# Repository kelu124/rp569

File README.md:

# rp569

An open hardware board (KiCad) that pairs a **Raspberry Pi RP2350B** with a **WCH CH569W**.
The RP2350B generates high-speed data and the CH569 streams it to a host over **USB 3.0**.

Status: **v1.0** (tag `v1.0`). Schematic complete, PCB **fully routed** (4-layer, 50×70 mm, rounded corners,
parts on both sides; 0 unconnected, 0 DRC errors) and **JLCPCB production files generated**. Before ordering:
USB pairs as coupled pairs, silkscreen cleanup, impedance check (see [`docs/layout.md`](docs/layout.md)).
First firmware for both chips in [`firmware/`](firmware/) (builds, not run on hardware yet).
[Schematic PDF](hardware/rp569-schematic.pdf). Documentation site: https://kelu124.github.io/rp569/ (GitHub Pages from `docs/`).

## Production files (JLCPCB)

| File | Use |
|---|---|
| [`hardware/jlcpcb/rp569-gerbers.zip`](hardware/jlcpcb/rp569-gerbers.zip) | PCB order (gerbers + drill) |
| [`hardware/jlcpcb/rp569-bom.csv`](hardware/jlcpcb/rp569-bom.csv) | Assembly BOM with LCSC part numbers |
| [`hardware/jlcpcb/rp569-cpl.csv`](hardware/jlcpcb/rp569-cpl.csv) | Assembly placement (CPL) |

Board to fabricate: [`hardware/rp569-routed.kicad_pcb`](hardware/rp569-routed.kicad_pcb). Regenerate the files
with `python3 hardware/gen/gen_fab.py`. Two parts are not stocked by JLCPCB and must be consigned: CH569W and the
Amphenol GSB343K33HR USB3 connector ([`docs/bom.md`](docs/bom.md)).

| Top | Bottom |
|---|---|
|  |  |

## Features

| Block | RP2350B | CH569W |
|-------|---------|--------|
| USB | USB 2.0 on USB-C (firmware, debug, test control) | USB 3.0 SuperSpeed, Micro-B connector |
| Storage | QSPI flash | SD card on the eMMC/SD controller |
| User I/O | RGB LED, 2 user buttons | RGB LED, 2 user buttons |
| Boot | BOOTSEL + RUN buttons | BOOT button + jumper (force the USB bootloader on a blank chip) |
| Breakout | I2C header for extra devices | I2C header (bit-banged GPIO) |

**Logic analyser**: 8 input pins on the RP2350B are sampled by PIO and streamed over the
parallel bus to the CH569, then to the host over USB 3.

**Power**: the RP2350B runs from either USB connector through a TI TPS2121 power mux, so neither back-feeds the
other. The CH569 is powered from its own USB3 VBUS through a load switch that the RP2350B controls, so
it can be power-cycled and forced into its bootloader during automated tests.

**Links between the two chips**
- 8-bit parallel bus with clock and handshake lines (8-bit because the CH569's 16-bit mode shares pins with the SD card; see [`specification.md`](specification.md) D-003): RP2350B PIO sends, CH569 HSPI receives.
- Shared I2C bus.
- UART.
- CH569 RESET# and boot-mode pins driven by the RP2350B, so the CH569 can be reflashed and
  power-cycled automatically during testing.

## Repository layout

| Path | Content |
|------|---------|
| `hardware/` | KiCad project, generated from `hardware/gen/board.py` (run `hardware/gen/build.sh`); `rp569-routed.kicad_pcb` = routed v1.0 board |
| `hardware/jlcpcb/` | JLCPCB production files: gerbers zip, BOM, CPL |
| `python/` | Host library: finds the RP2350/CH569 ports by VID/PID/product/UID, one method per firmware command (`python/README.md`) |
| `firmware/` | `rp2350/` USB command line (LED, `dfu`, CH569 power/boot/link), `ch569/` USB3 serial + SD drive with RP2350 link echo; see `firmware/README.md` |
| `datasheet/` | Datasheets as PDF and Markdown (see `datasheet/README.md`) |
| `docs/` | GitHub Pages site root (`index.md`, `_config.yml`): `architecture.md`, `production.md`, `pinmap.md` (RP2350B ↔ CH569 pin map), `power.md`, `layout.md`, `bom.md` (JLCPCB BOM), `ch569-hardware-notes.md`, `hadposts/` (Hackaday log drafts) |
| `project/` | Reference projects: [HydraUSB3](https://github.com/hydrausb3), [phantomdrive](https://github.com/o7-machinehum/phantomdrive) (see `project/README.md`) |
| `specification.md` | Requirements (R-xx) and design decisions (D-xxx) |
| `CLAUDE.md`, `.claude/` | Project context, todo/done logs, commit log |

## References

- [HydraUSB3](https://github.com/hydrausb3): open-source CH569 dev kit, firmware and HSPI/USB3 drivers.
- [phantomdrive](https://github.com/o7-machinehum/phantomdrive): open-source CH569W encrypted USB3 drive with SD card, KiCad sources.
- [RP2350 datasheet](https://datasheets.raspberrypi.com/rp2350/rp2350-datasheet.pdf) and
  [hardware design guide](https://datasheets.raspberrypi.com/rp2350/hardware-design-with-rp2350.pdf).

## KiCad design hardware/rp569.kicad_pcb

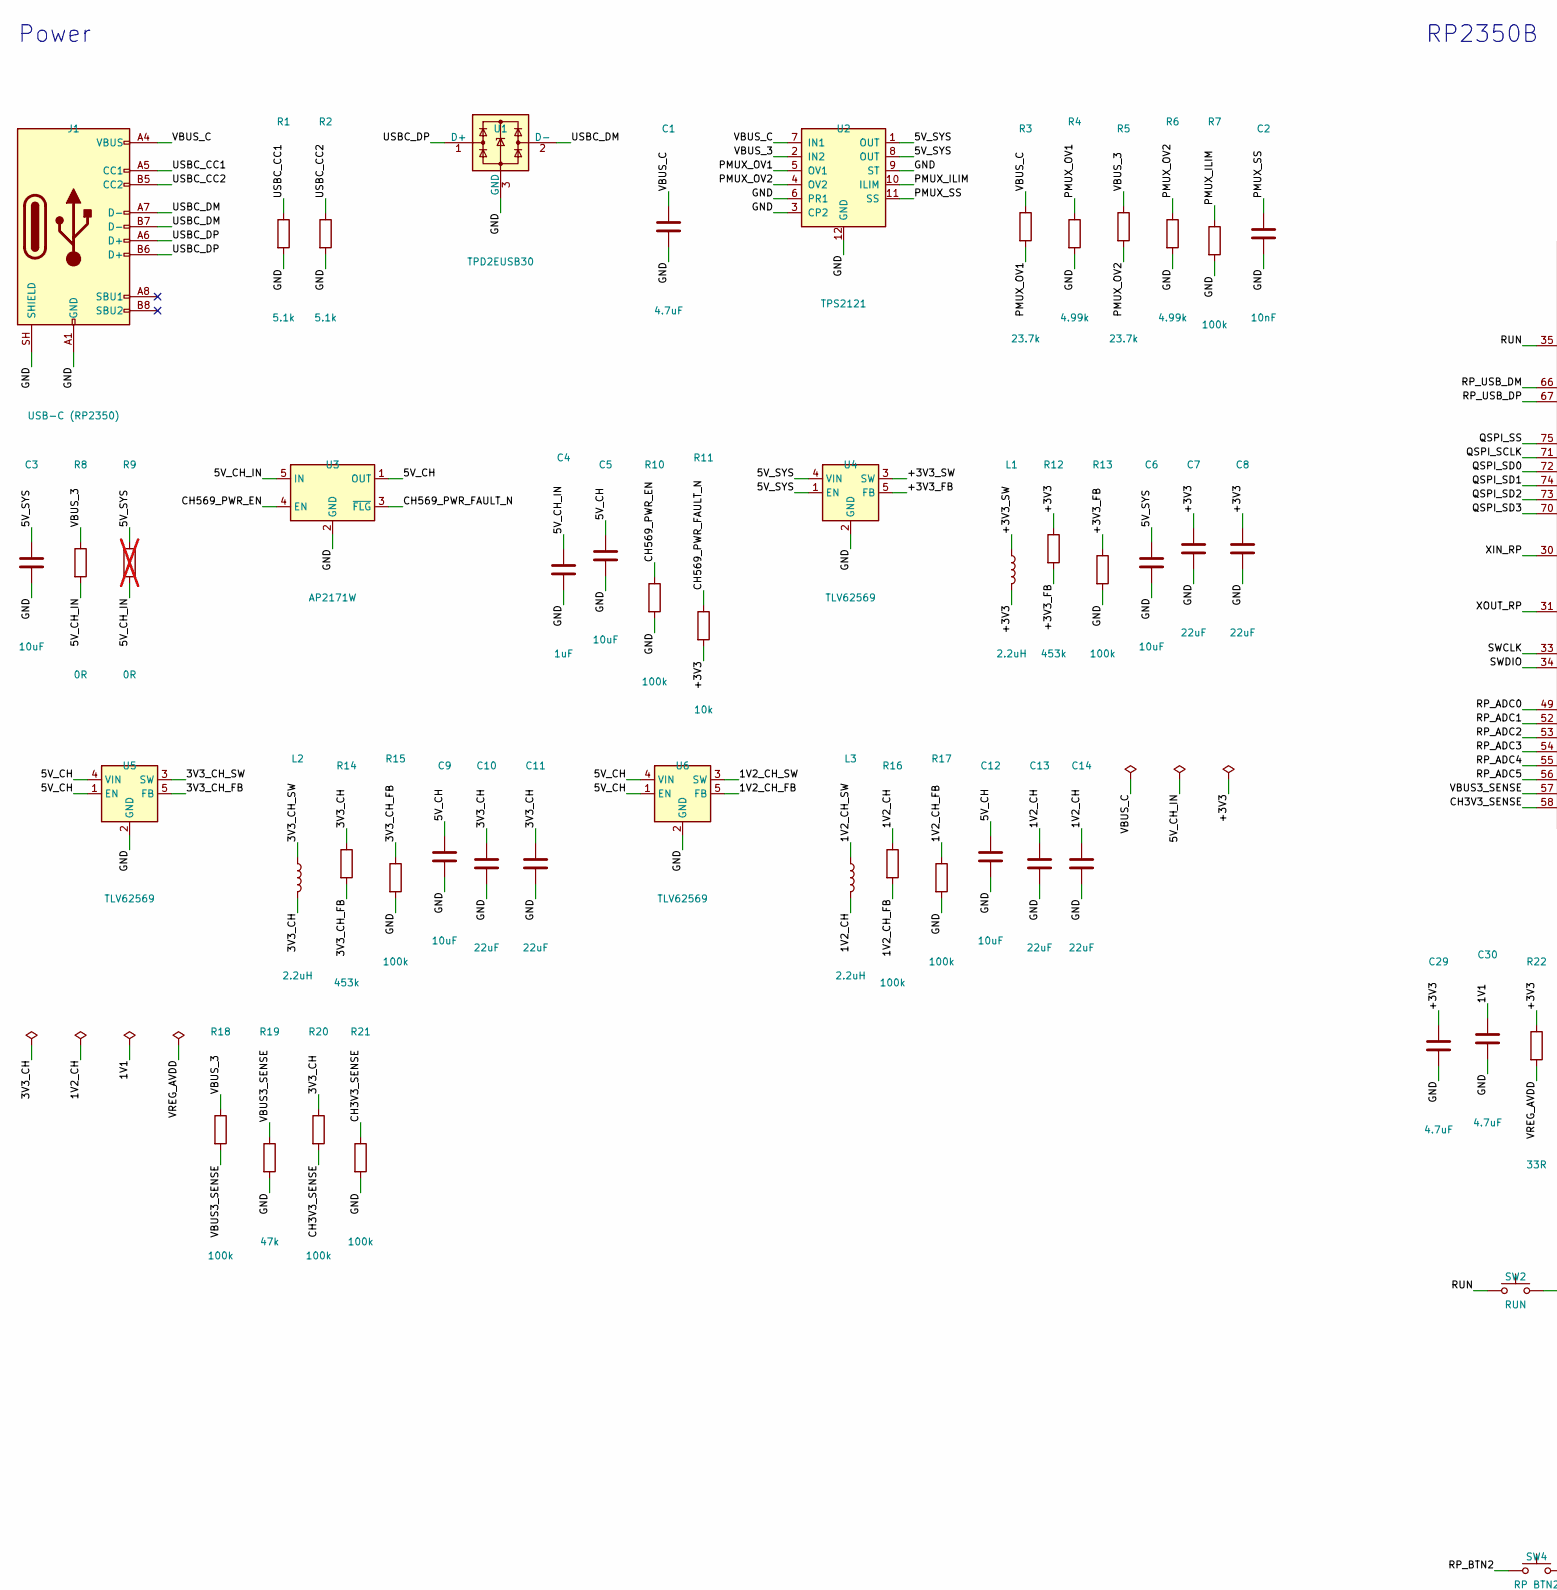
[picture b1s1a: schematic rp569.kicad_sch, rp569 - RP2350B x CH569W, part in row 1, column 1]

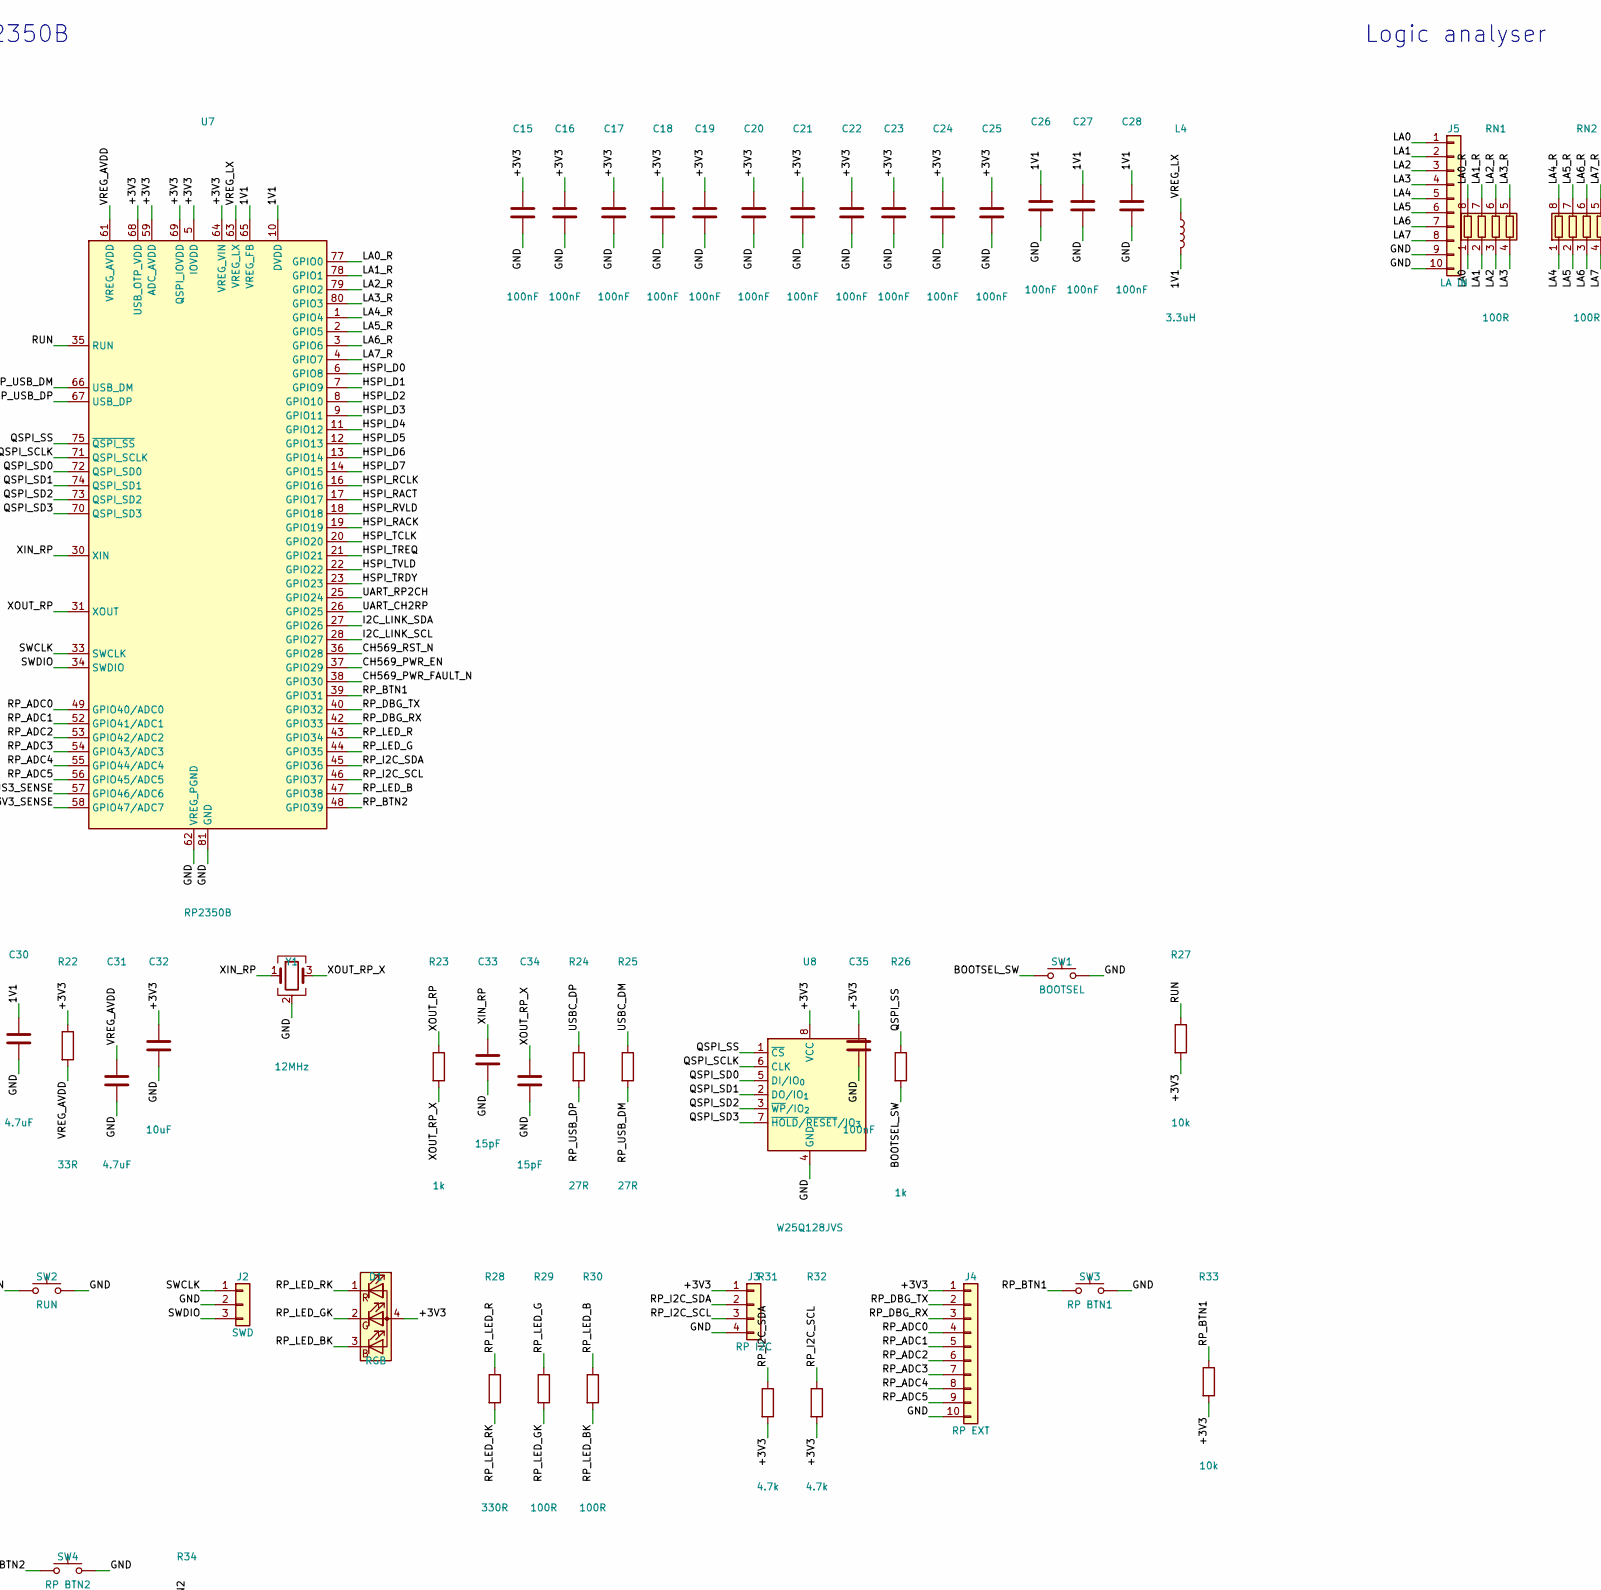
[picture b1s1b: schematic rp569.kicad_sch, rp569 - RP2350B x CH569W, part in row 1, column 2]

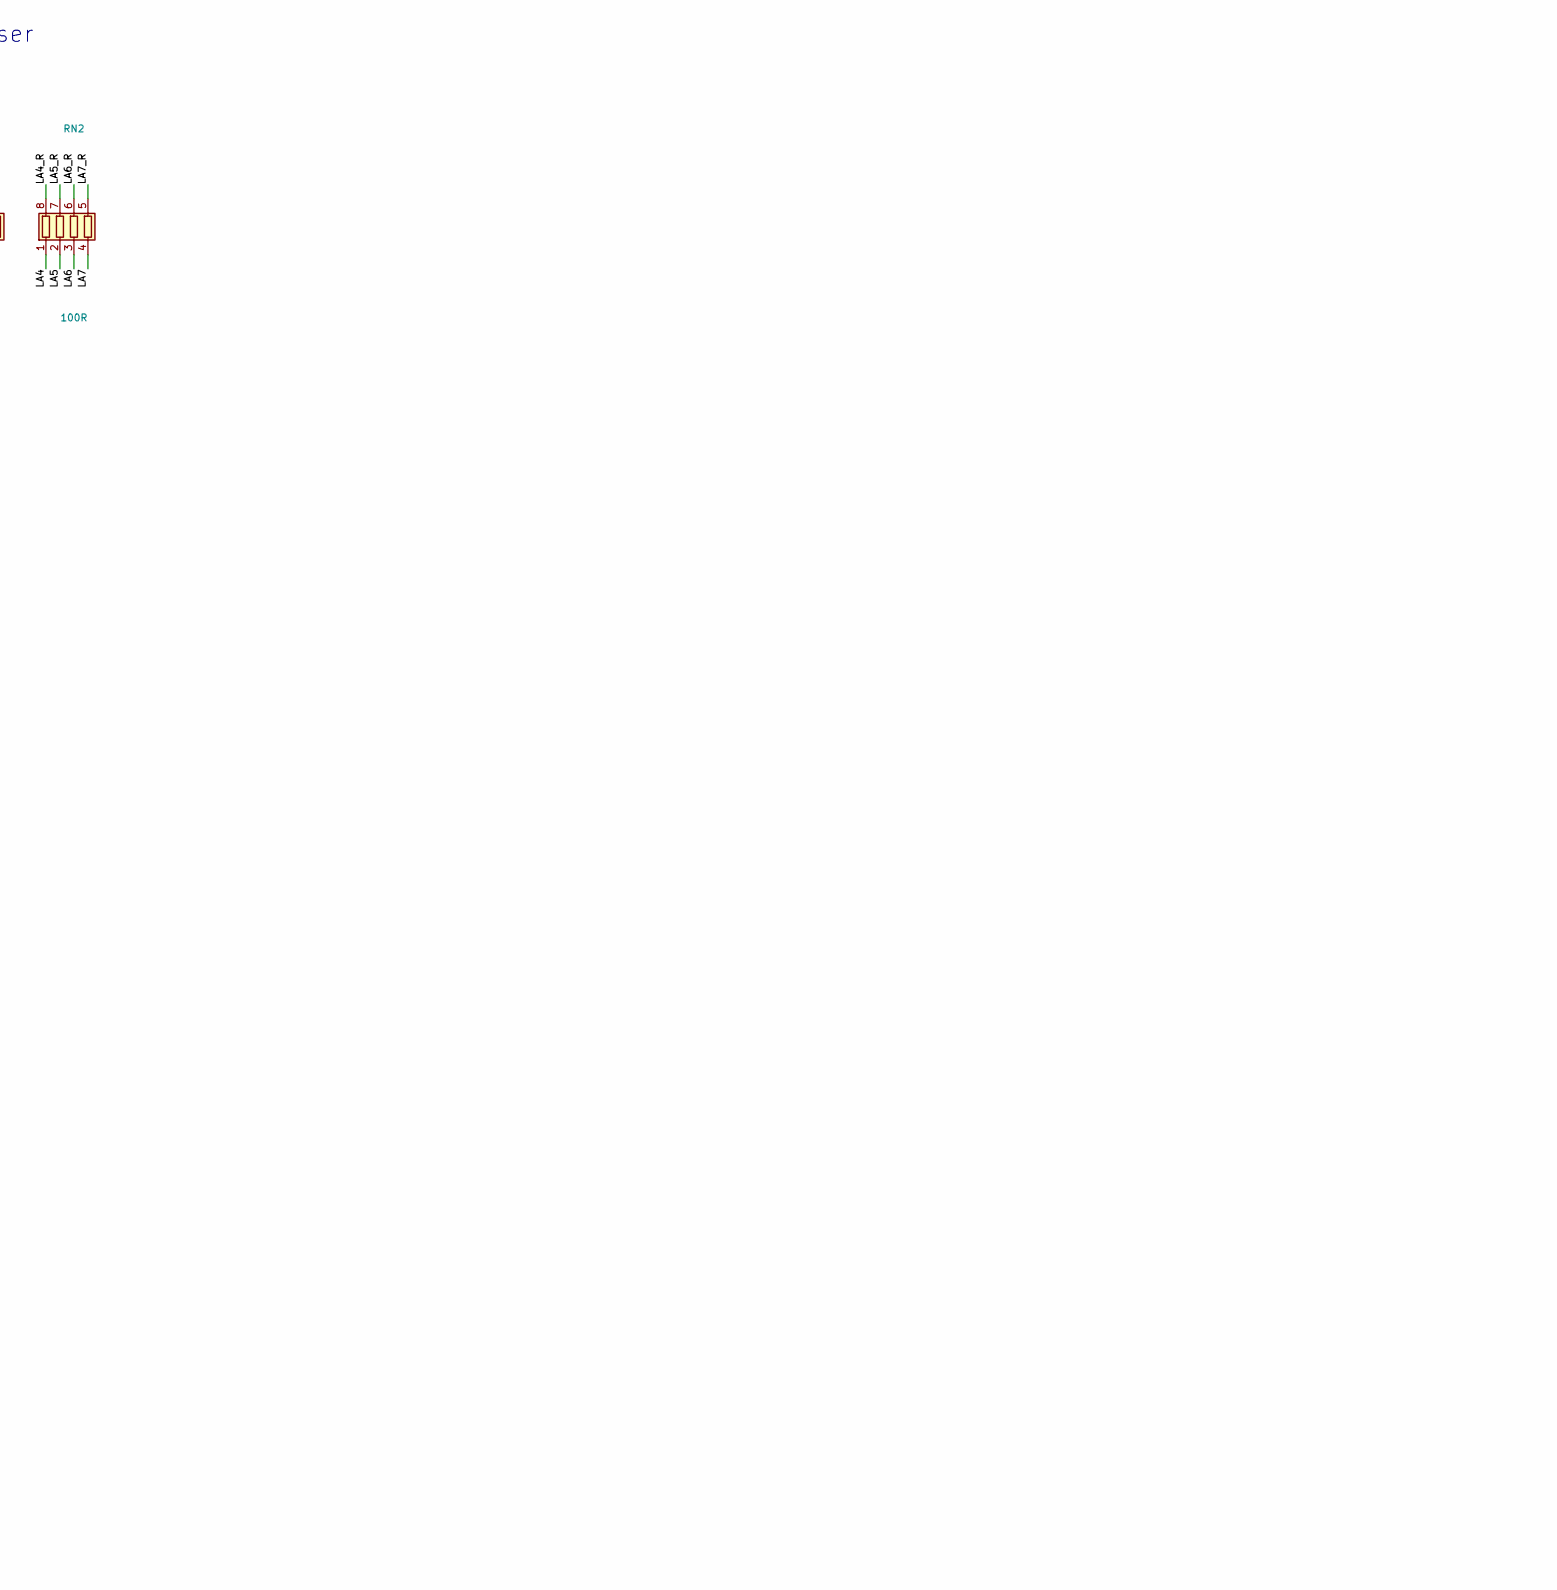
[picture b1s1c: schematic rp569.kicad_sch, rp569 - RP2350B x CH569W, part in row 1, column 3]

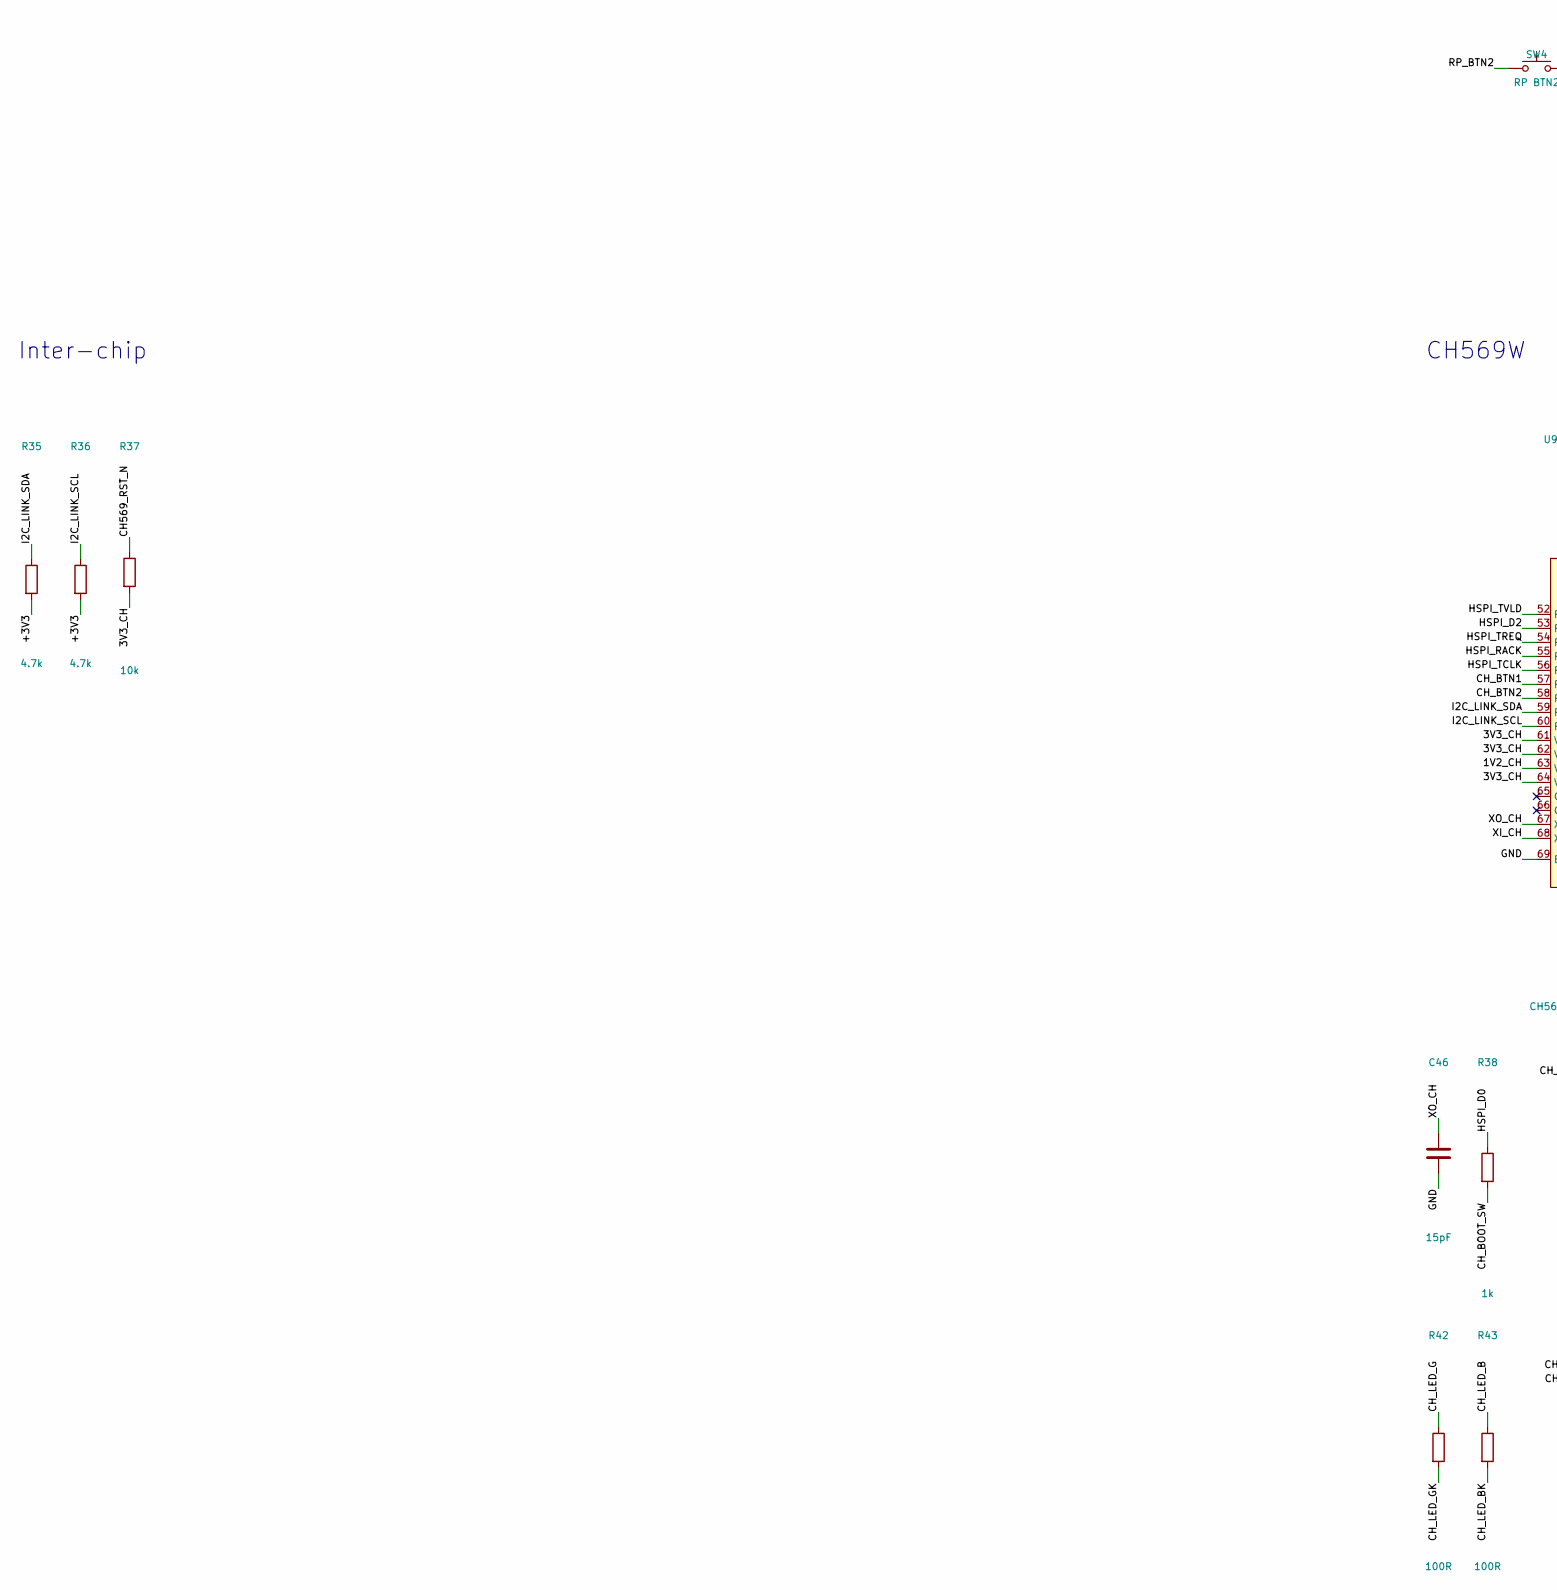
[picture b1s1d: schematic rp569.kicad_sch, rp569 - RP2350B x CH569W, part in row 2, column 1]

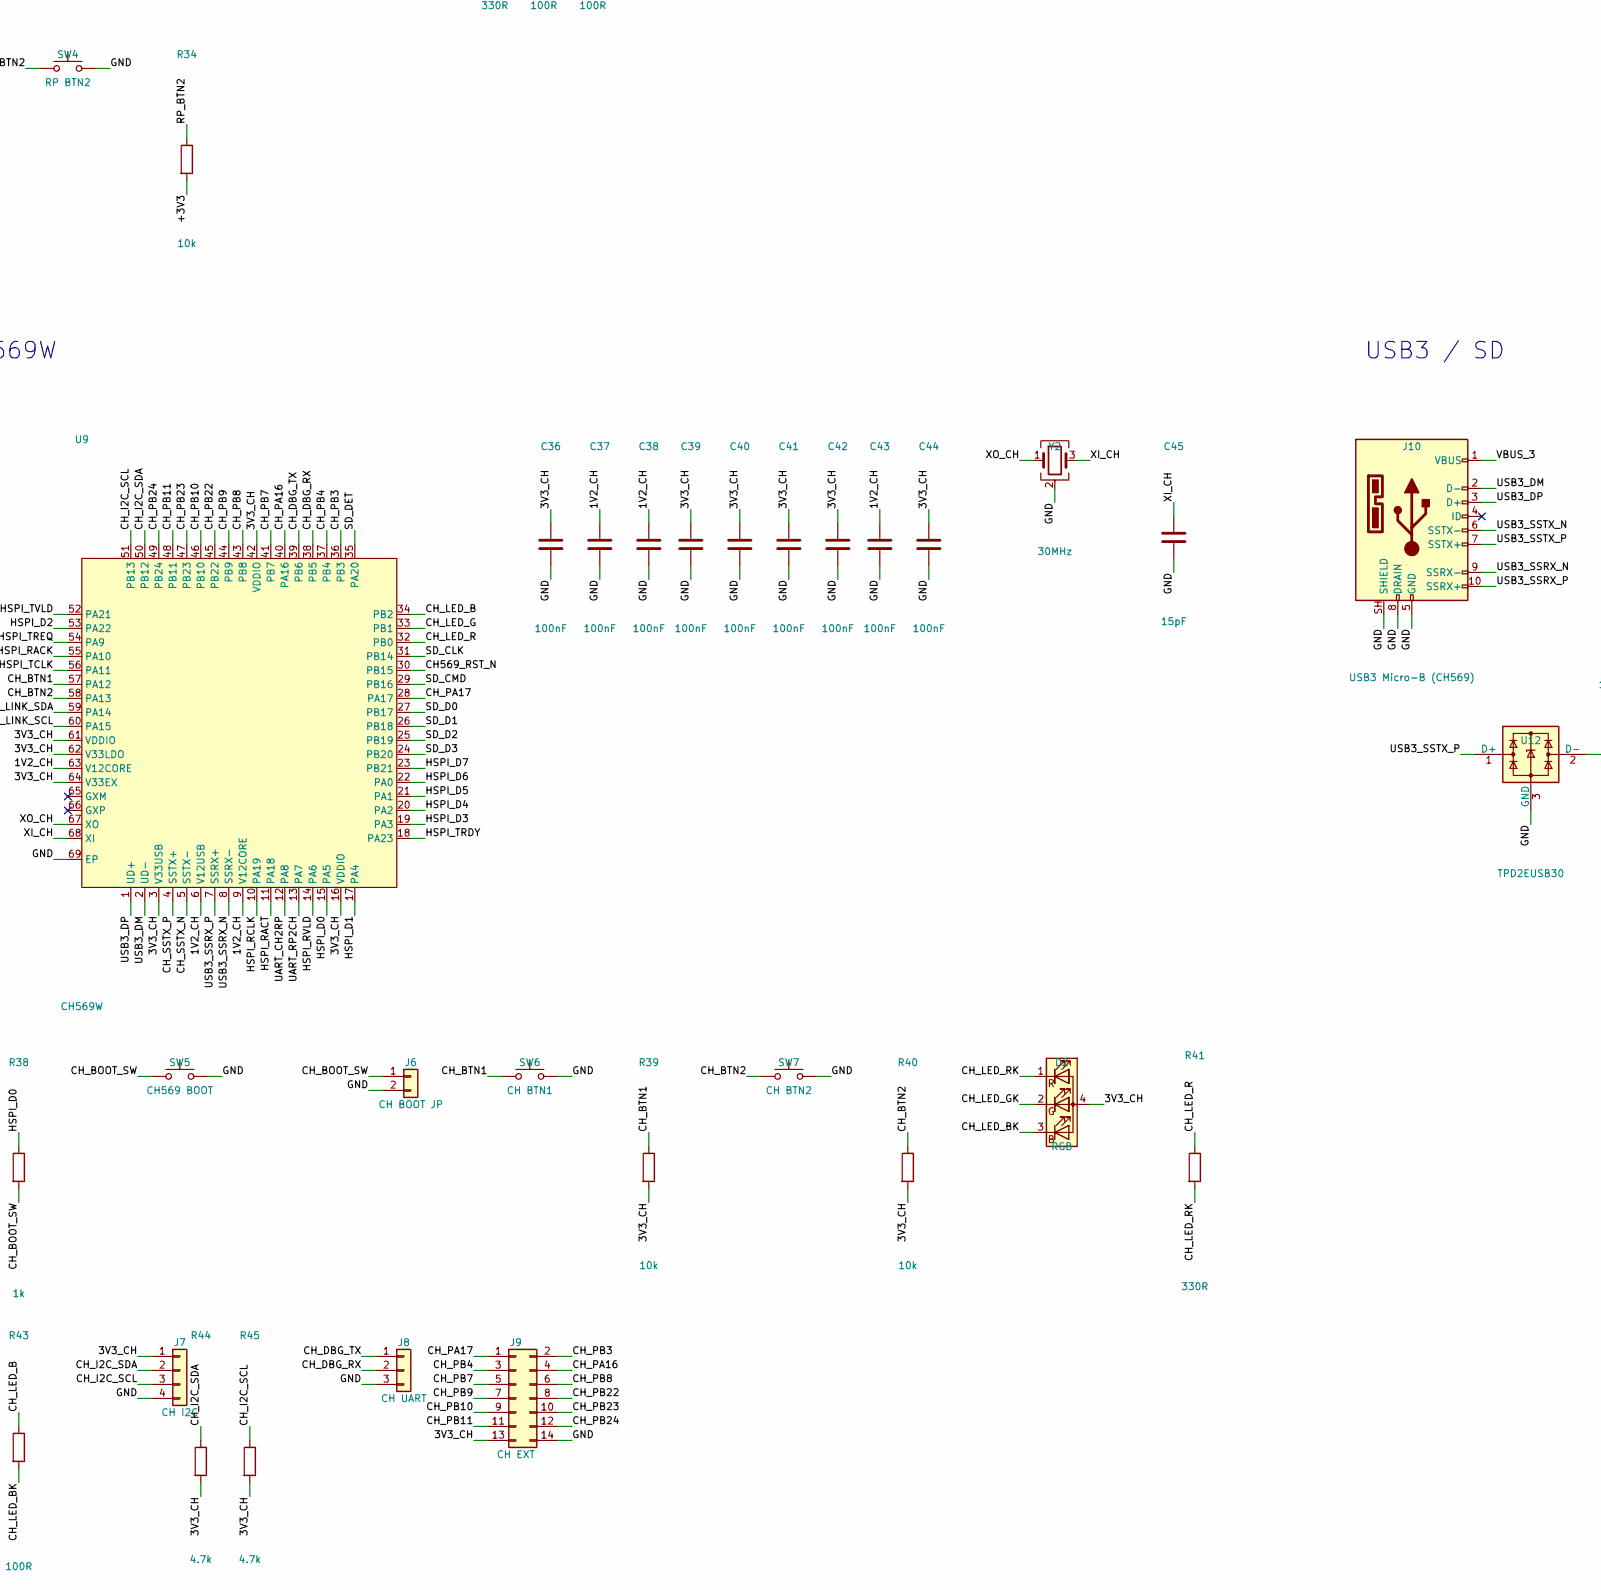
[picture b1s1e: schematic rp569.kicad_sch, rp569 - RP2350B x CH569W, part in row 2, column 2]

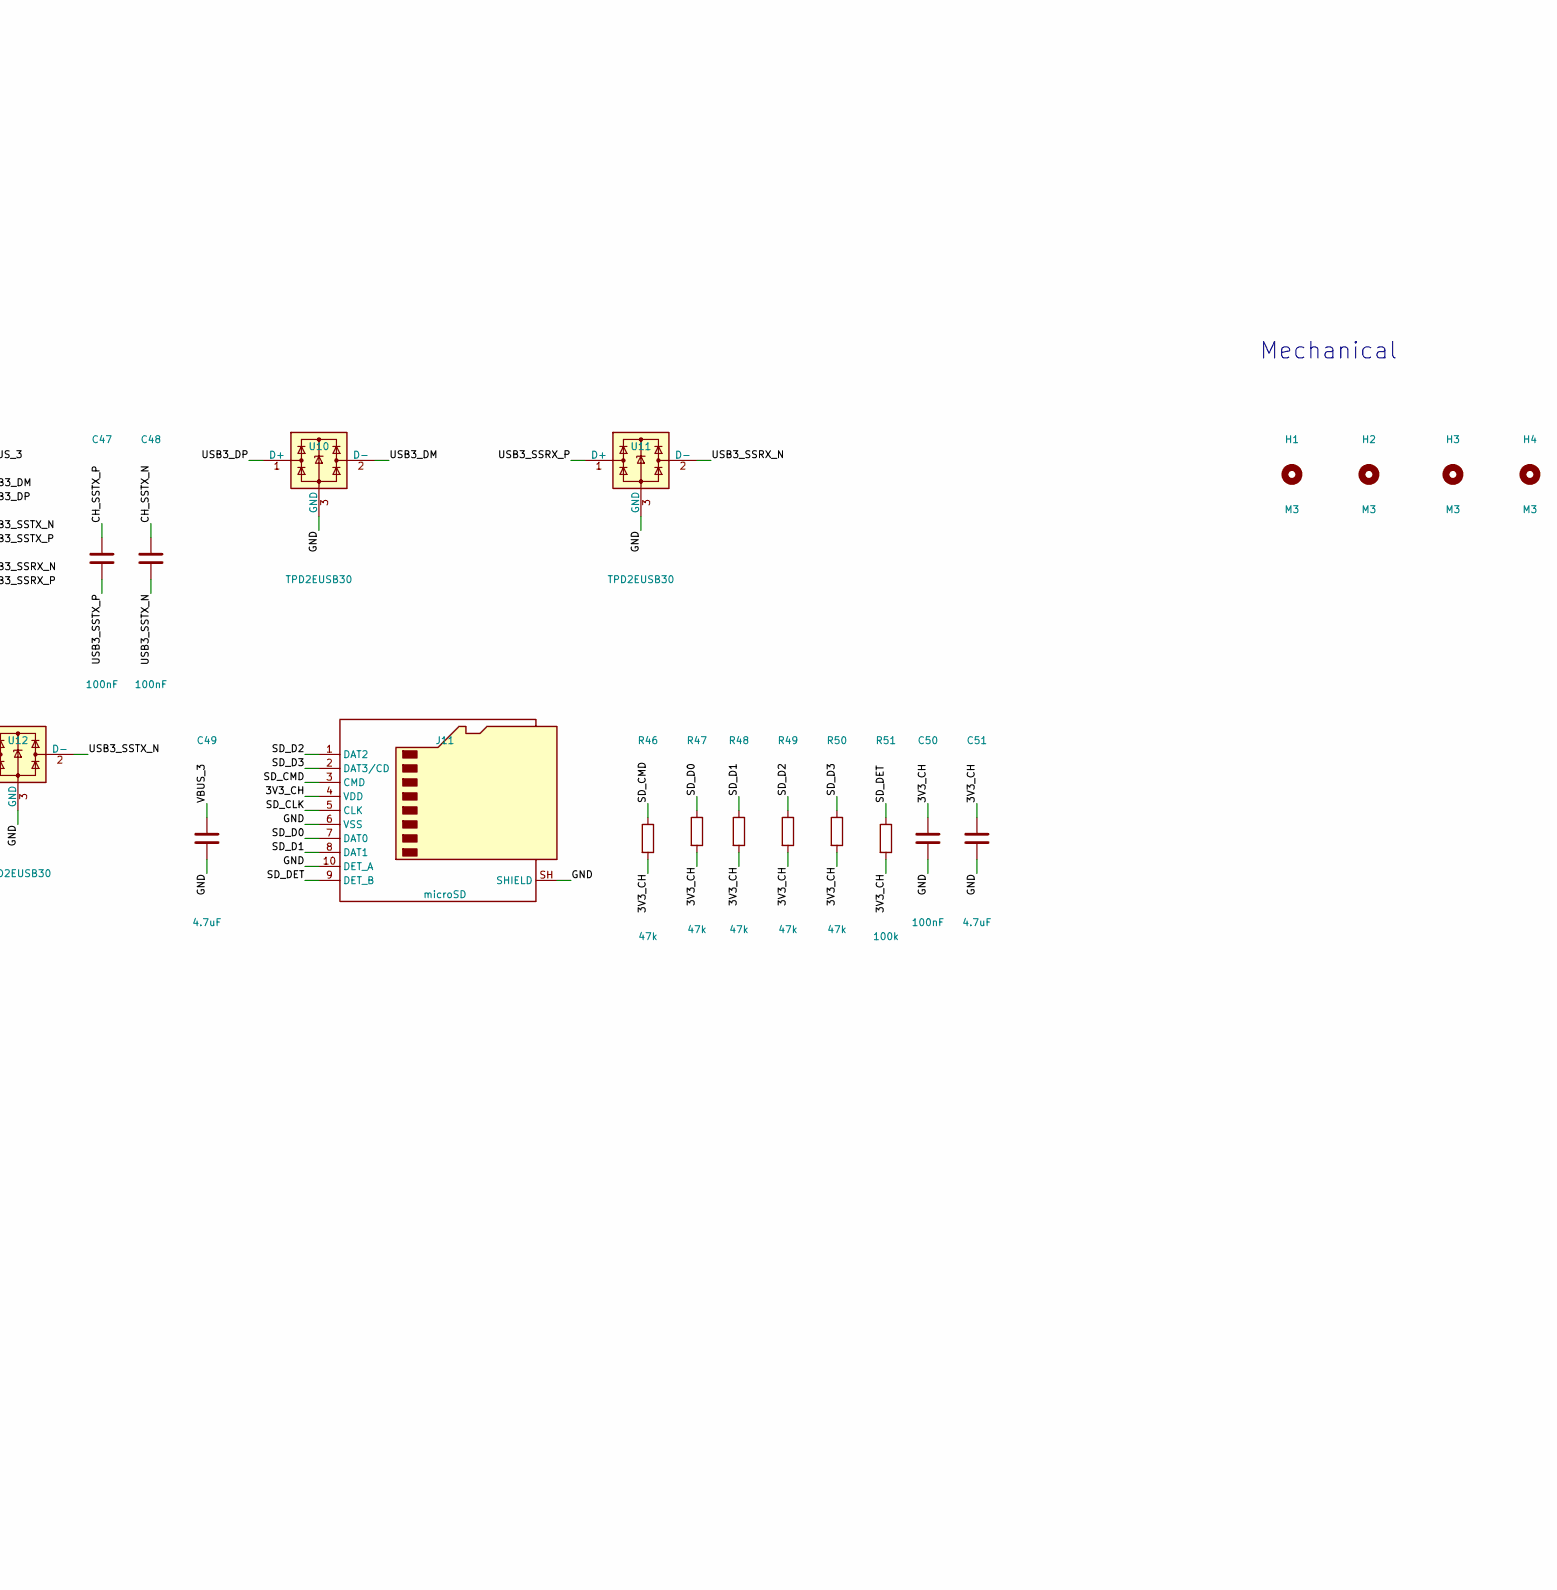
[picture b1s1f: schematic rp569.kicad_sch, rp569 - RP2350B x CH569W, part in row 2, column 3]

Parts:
C1, C29, C30, C31, C49, C51: 4.7uF; C_0402_1005Metric; MPN CL05A475MP5NRNC; LCSC C23733
C2: 10nF; C_0402_1005Metric; MPN CL05B103KB5NNNC; LCSC C15195
C3, C5, C6, C9, C12, C32: 10uF; C_0805_2012Metric; MPN CL21A106KAYNNNE; LCSC C15850
C4: 1uF; C_0402_1005Metric; MPN CL05A105KA5NQNC; LCSC C52923
C7, C8, C10, C11, C13, C14: 22uF; C_0805_2012Metric; MPN CL21A226MAQNNNE; LCSC C45783
C15, C16, C17, C18, C19, C20, C21, C22, C23, C24, C25, C26, C27, C28, C35, C36, C37, C38, C39, C40, C41, C42, C43, C44, C47, C48, C50: 100nF; C_0402_1005Metric; MPN CL05B104KO5NNNC; LCSC C1525
C33, C34, C45, C46: 15pF; C_0402_1005Metric; MPN 0402CG150J500NT; LCSC C1548
D1, D2: RGB; LED_LiteOn_LTST-C19HE1WT; MPN LTST-C19HE1WT; LCSC C458749
H1, H2, H3, H4: M3; MountingHole_3.2mm_M3
J1: USB-C (RP2350); USB_C_Receptacle_HRO_TYPE-C-31-M-12; MPN TYPE-C-31-M-12; LCSC C165948
J2: SWD; PinHeader_1x03_P2.54mm_Vertical; MPN 2.54-1*3P; LCSC C49257
J3: RP I2C; PinHeader_1x04_P2.54mm_Vertical; MPN PZ254V-11-04P; LCSC C492403
J4: RP EXT; PinHeader_1x10_P2.54mm_Vertical; MPN PZ254V-11-10P; LCSC C492409
J5: LA IN; PinHeader_1x10_P2.54mm_Vertical; MPN PZ254V-11-10P; LCSC C492409
J6: CH BOOT JP; PinHeader_1x02_P2.54mm_Vertical; MPN PZ254V-11-02P; LCSC C492401
J7: CH I2C; PinHeader_1x04_P2.54mm_Vertical; MPN PZ254V-11-04P; LCSC C492403
J8: CH UART; PinHeader_1x03_P2.54mm_Vertical; MPN 2.54-1*3P; LCSC C49257
J9: CH EXT; PinHeader_2x07_P2.54mm_Vertical; MPN PZ254V-12-14P; LCSC C492424
J10: USB3 Micro-B (CH569); USB3_Micro-B_Amphenol_GSB343K33HR; MPN GSB343K33HR
J11: microSD; microSD_HC_Hirose_DM3AT-SF-PEJM5; MPN DM3AT-SF-PEJM5; LCSC C114218
L1, L2, L3: 2.2uH; L_Changjiang_FTC303015D; MPN FTC303020D2R2MBCA; LCSC C7423318
L4: 3.3uH; L_Cenker_CKCS201610; MPN AOTA-B201610S3R3-101-T; LCSC C42411119
R1, R2: 5.1k; R_0402_1005Metric; MPN 0402WGF5101TCE; LCSC C25905
R3, R5: 23.7k; R_0402_1005Metric; MPN AC0402FR-0723K7L; LCSC C226363
R4, R6: 4.99k; R_0402_1005Metric; MPN 0402WGF4991TCE; LCSC C25903
R7, R10, R13, R15, R16, R17, R18, R20, R21, R51: 100k; R_0402_1005Metric; MPN 0402WGF1003TCE; LCSC C25741
R8: 0R; R_0402_1005Metric; MPN 0402WGF0000TCE; LCSC C17168
R9: 0R; R_0402_1005Metric; MPN 0402WGF0000TCE; LCSC C17168; not fitted
R11, R27, R33, R34, R37, R39, R40: 10k; R_0402_1005Metric; MPN 0402WGF1002TCE; LCSC C25744
R12, R14: 453k; R_0402_1005Metric; MPN 0402WGF4533TCE; LCSC C27009
R19, R46, R47, R48, R49, R50: 47k; R_0402_1005Metric; MPN 0402WGF4702TCE; LCSC C25792
R22: 33R; R_0402_1005Metric; MPN 0402WGF330JTCE; LCSC C25105
R23, R26, R38: 1k; R_0402_1005Metric; MPN 0402WGF1001TCE; LCSC C11702
R24, R25: 27R; R_0402_1005Metric; MPN RC0402FR-0727RL; LCSC C138021
R28, R41: 330R; R_0402_1005Metric; MPN 0402WGF3300TCE; LCSC C25104
R29, R30, R42, R43: 100R; R_0402_1005Metric; MPN 0402WGF1000TCE; LCSC C25076
R31, R32, R35, R36, R44, R45: 4.7k; R_0402_1005Metric; MPN 0402WGF4701TCE; LCSC C25900
RN1, RN2: 100R; R_Array_Convex_4x0402; MPN 4D02WGJ0101TCE; LCSC C48442
SW1: BOOTSEL; SW_SPST_PTS810; MPN PTS810SJG250SMTRLFS; LCSC C221895
SW2: RUN; SW_SPST_PTS810; MPN PTS810SJG250SMTRLFS; LCSC C221895
SW3: RP BTN1; SW_SPST_PTS810; MPN PTS810SJG250SMTRLFS; LCSC C221895
SW4: RP BTN2; SW_SPST_PTS810; MPN PTS810SJG250SMTRLFS; LCSC C221895
SW5: CH569 BOOT; SW_SPST_PTS810; MPN PTS810SJG250SMTRLFS; LCSC C221895
SW6: CH BTN1; SW_SPST_PTS810; MPN PTS810SJG250SMTRLFS; LCSC C221895
SW7: CH BTN2; SW_SPST_PTS810; MPN PTS810SJG250SMTRLFS; LCSC C221895
U1, U10, U11, U12: TPD2EUSB30; Texas_DRT-3; MPN TPD2EUSB30DRTR; LCSC C97502
U2: TPS2121; TI_RUX0012A_VQFN-HR-12_2x2.5mm; MPN TPS2121RUXR; LCSC C485916
U3: AP2171W; SOT-23-5; MPN AP2171WG-7; LCSC C110466
U4, U5, U6: TLV62569; SOT-23-5; MPN TLV62569DBVR; LCSC C141836
U7: RP2350B; QFN-80-1EP_10x10mm_P0.4mm_EP3.4x3.4mm; MPN RP2350B; LCSC C42415655
U8: W25Q128JVS; SOIC-8_5.3x5.3mm_P1.27mm; MPN W25Q128JVSIQ; LCSC C97521
U9: CH569W; QFN-68-1EP_8x8mm_P0.4mm_EP5.2x5.2mm; MPN CH569W
Y1: 12MHz; Crystal_SMD_3225-4Pin_3.2x2.5mm; MPN ABM8-272-T3; LCSC C20625731
Y2: 30MHz; Crystal_SMD_3225-4Pin_3.2x2.5mm; MPN X322530MOB4SI; LCSC C70592

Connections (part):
/1V1: C26.1, C27.1, C28.1, C30.1, L4.2, U7.10 (DVDD), U7.32 (DVDD), U7.51 (DVDD), U7.65 (VREG_FB)
/1V2_CH: C13.1, C14.1, C37.1, C38.1, C43.1, L3.2, R16.1, U9.6 (V12USB), U9.9 (V12CORE), U9.63 (V12CORE)
/1V2_CH_FB: R16.2, R17.1, U6.5 (FB)
/1V2_CH_SW: L3.1, U6.3 (SW)
/3V3_CH: C10.1, C11.1, C36.1, C39.1, C40.1, C41.1, C42.1, C44.1, C50.1, C51.1, D2.4 (A), J7.1, J9.13, J11.4 (VDD), L2.2, R14.1, R20.1, R37.2, R39.2, R40.2, R44.2, R45.2, R46.2, R47.2, R48.2, R49.2, R50.2, R51.2, U9.3 (V33USB), U9.16 (VDDIO), U9.42 (VDDIO), U9.61 (VDDIO), U9.62 (V33LDO), U9.64 (V33EX)
/3V3_CH_FB: R14.2, R15.1, U5.5 (FB)
/3V3_CH_SW: L2.1, U5.3 (SW)
/5V_CH: C5.1, C9.1, C12.1, U3.1 (OUT), U5.1 (EN), U5.4 (VIN), U6.1 (EN), U6.4 (VIN)
/5V_CH_IN: C4.1, R8.2, R9.2, U3.5 (IN)
/5V_SYS: C3.1, C6.1, R9.1, U2.1 (OUT), U2.8 (OUT), U4.1 (EN), U4.4 (VIN)
/+3V3: C7.1, C8.1, C15.1, C16.1, C17.1, C18.1, C19.1, C20.1, C21.1, C22.1, C23.1, C24.1, C25.1, C29.1, C32.1, C35.1, D1.4 (A), J3.1, J4.1, L1.2, R11.2, R12.1, R22.1, R27.2, R31.2, R32.2, R33.2, R34.2, R35.2, R36.2, U7.5 (IOVDD), U7.15 (IOVDD), U7.24 (IOVDD), U7.29 (IOVDD), U7.41 (IOVDD), U7.50 (IOVDD), U7.59 (ADC_AVDD), U7.60 (IOVDD), U7.64 (VREG_VIN), U7.68 (USB_OTP_VDD), U7.69 (QSPI_IOVDD), U7.76 (IOVDD), U8.8 (VCC)
/+3V3_FB: R12.2, R13.1, U4.5 (FB)
/+3V3_SW: L1.1, U4.3 (SW)
/BOOTSEL_SW: R26.2, SW1.1
/CH3V3_SENSE: R20.2, R21.1, U7.58 (GPIO47/ADC7)
/CH569_PWR_EN: R10.1, U3.4 (EN), U7.37 (GPIO29)
/CH569_PWR_FAULT_N: R11.1, U3.3 (~FLG), U7.38 (GPIO30)
/CH569_RST_N: R37.1, U7.36 (GPIO28), U9.30 (PB15)
/CH_BOOT_SW: J6.1, R38.2, SW5.1
/CH_BTN1: R39.1, SW6.1, U9.57 (PA12)
/CH_BTN2: R40.1, SW7.1, U9.58 (PA13)
/CH_DBG_RX: J8.2, U9.38 (PB5)
/CH_DBG_TX: J8.1, U9.39 (PB6)
/CH_I2C_SCL: J7.3, R45.1, U9.51 (PB13)
/CH_I2C_SDA: J7.2, R44.1, U9.50 (PB12)
/CH_LED_B: R43.1, U9.34 (PB2)
/CH_LED_BK: D2.3 (BK), R43.2
/CH_LED_G: R42.1, U9.33 (PB1)
/CH_LED_GK: D2.2 (GK), R42.2
/CH_LED_R: R41.1, U9.32 (PB0)
/CH_LED_RK: D2.1 (RK), R41.2
/CH_PA16: J9.4, U9.40 (PA16)
/CH_PA17: J9.1, U9.28 (PA17)
/CH_PB3: J9.2, U9.36 (PB3)
/CH_PB4: J9.3, U9.37 (PB4)
/CH_PB7: J9.5, U9.41 (PB7)
/CH_PB8: J9.6, U9.43 (PB8)
/CH_PB9: J9.7, U9.44 (PB9)
/CH_PB10: J9.9, U9.46 (PB10)
/CH_PB11: J9.11, U9.48 (PB11)
/CH_PB22: J9.8, U9.45 (PB22)
/CH_PB23: J9.10, U9.47 (PB23)
/CH_PB24: J9.12, U9.49 (PB24)
/CH_SSTX_N: C48.1, U9.5 (SSTX-)
/CH_SSTX_P: C47.1, U9.4 (SSTX+)
/GND: C1.2, C2.2, C3.2, C4.2, C5.2, C6.2, C7.2, C8.2, C9.2, C10.2, C11.2, C12.2, C13.2, C14.2, C15.2, C16.2, C17.2, C18.2, C19.2, C20.2, C21.2, C22.2, C23.2, C24.2, C25.2, C26.2, C27.2, C28.2, C29.2, C30.2, C31.2, C32.2, C33.2, C34.2, C35.2, C36.2, C37.2, C38.2, C39.2, C40.2, C41.2, C42.2, C43.2, C44.2, C45.2, C46.2, C49.2, C50.2, C51.2, J1.A1 (GND), J1.A12 (GND), J1.B1 (GND), J1.B12 (GND), J1.SH (SHIELD), J2.2, J3.4, J4.10, J5.9, J5.10, J6.2, J7.4, J8.3, J9.14, J10.5 (GND), J10.8 (DRAIN), J10.SH (SHIELD), J11.6 (VSS), J11.10 (DET_A), J11.SH (SHIELD), R1.2, R2.2, R4.2, R6.2, R7.2, R10.2, R13.2, R15.2, R17.2, R19.2, R21.2, SW1.2, SW2.2, SW3.2, SW4.2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
/HSPI_D0: R38.1, U7.6 (GPIO8), U9.15 (PA5)
/HSPI_D1: U7.7 (GPIO9), U9.17 (PA4)
/HSPI_D2: U7.8 (GPIO10), U9.53 (PA22)
/HSPI_D3: U7.9 (GPIO11), U9.19 (PA3)
/HSPI_D4: U7.11 (GPIO12), U9.20 (PA2)
/HSPI_D5: U7.12 (GPIO13), U9.21 (PA1)
/HSPI_D6: U7.13 (GPIO14), U9.22 (PA0)
/HSPI_D7: U7.14 (GPIO15), U9.23 (PB21)
/HSPI_RACK: U7.19 (GPIO19), U9.55 (PA10)
/HSPI_RACT: U7.17 (GPIO17), U9.11 (PA18)
/HSPI_RCLK: U7.16 (GPIO16), U9.10 (PA19)
/HSPI_RVLD: U7.18 (GPIO18), U9.14 (PA6)
/HSPI_TCLK: U7.20 (GPIO20), U9.56 (PA11)
/HSPI_TRDY: U7.23 (GPIO23), U9.18 (PA23)
/HSPI_TREQ: U7.21 (GPIO21), U9.54 (PA9)
/HSPI_TVLD: U7.22 (GPIO22), U9.52 (PA21)
/I2C_LINK_SCL: R36.1, U7.28 (GPIO27), U9.60 (PA15)
/I2C_LINK_SDA: R35.1, U7.27 (GPIO26), U9.59 (PA14)
/LA0: J5.1, RN1.1 (R1.1)
/LA0_R: RN1.8 (R1.2), U7.77 (GPIO0)
/LA1: J5.2, RN1.2 (R2.1)
/LA1_R: RN1.7 (R2.2), U7.78 (GPIO1)
/LA2: J5.3, RN1.3 (R3.1)
/LA2_R: RN1.6 (R3.2), U7.79 (GPIO2)
/LA3: J5.4, RN1.4 (R4.1)
/LA3_R: RN1.5 (R4.2), U7.80 (GPIO3)
/LA4: J5.5, RN2.1 (R1.1)
/LA4_R: RN2.8 (R1.2), U7.1 (GPIO4)
/LA5: J5.6, RN2.2 (R2.1)
/LA5_R: RN2.7 (R2.2), U7.2 (GPIO5)
/LA6: J5.7, RN2.3 (R3.1)
/LA6_R: RN2.6 (R3.2), U7.3 (GPIO6)
/LA7: J5.8, RN2.4 (R4.1)
/LA7_R: RN2.5 (R4.2), U7.4 (GPIO7)
/PMUX_ILIM: R7.1, U2.10 (ILIM)
/PMUX_OV1: R3.2, R4.1, U2.5 (OV1)
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
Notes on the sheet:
Power
RP2350B
Logic analyser
Inter-chip
CH569W
USB3 / SD
Mechanical

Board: 4 copper layers, 146 parts (62 on the bottom side), 142 nets, no tracks yet.

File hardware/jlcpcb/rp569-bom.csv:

Comment,Designator,Footprint,LCSC Part #,MPN,Qty,Note
USB-C (RP2350),J1,USB_C_Receptacle_HRO_TYPE-C-31-M-12,C165948,TYPE-C-31-M-12,1,
5.1k,"R1,R2",R_0402_1005Metric,C25905,0402WGF5101TCE,2,
TPD2EUSB30,"U1,U10,U11,U12",Texas_DRT-3,C97502,TPD2EUSB30DRTR,4,
4.7uF,"C1,C29,C30,C31,C49,C51",C_0402_1005Metric,C23733,CL05A475MP5NRNC,6,
TPS2121,U2,TI_RUX0012A_VQFN-HR-12_2x2.5mm,C485916,TPS2121RUXR,1,
23.7k,"R3,R5",R_0402_1005Metric,C226363,AC0402FR-0723K7L,2,
4.99k,"R4,R6",R_0402_1005Metric,C25903,0402WGF4991TCE,2,
100k,"R7,R10,R13,R15,R16,R17,R18,R20,R21,R51",R_0402_1005Metric,C25741,0402WGF1003TCE,10,
10nF,C2,C_0402_1005Metric,C15195,CL05B103KB5NNNC,1,
10uF,"C3,C5,C6,C9,C12,C32",C_0805_2012Metric,C15850,CL21A106KAYNNNE,6,
0R,R8,R_0402_1005Metric,C17168,0402WGF0000TCE,1,
AP2171W,U3,SOT-23-5,C110466,AP2171WG-7,1,
1uF,C4,C_0402_1005Metric,C52923,CL05A105KA5NQNC,1,
10k,"R11,R27,R33,R34,R37,R39,R40",R_0402_1005Metric,C25744,0402WGF1002TCE,7,
TLV62569,"U4,U5,U6",SOT-23-5,C141836,TLV62569DBVR,3,
2.2uH,"L1,L2,L3",L_Changjiang_FTC303015D,C7423318,FTC303020D2R2MBCA,3,
453k,"R12,R14",R_0402_1005Metric,C27009,0402WGF4533TCE,2,
22uF,"C7,C8,C10,C11,C13,C14",C_0805_2012Metric,C45783,CL21A226MAQNNNE,6,
47k,"R19,R46,R47,R48,R49,R50",R_0402_1005Metric,C25792,0402WGF4702TCE,6,
RP2350B,U7,QFN-80-1EP_10x10mm_P0.4mm_EP3.4x3.4mm,C42415655,RP2350B,1,
100nF,"C15,C16,C17,C18,C19,C20,C21,C22,C23,C24,C25,C26,C27,C28,C35,C36,C37,C38,C39,C40,C41,C42,C43,C44,C47,C48,C50",C_0402_1005Metric,C1525,CL05B104KO5NNNC,27,
3.3uH,L4,L_Cenker_CKCS201610,C42411119,AOTA-B201610S3R3-101-T,1,
33R,R22,R_0402_1005Metric,C25105,0402WGF330JTCE,1,
12MHz,Y1,Crystal_SMD_3225-4Pin_3.2x2.5mm,C20625731,ABM8-272-T3,1,
1k,"R23,R26,R38",R_0402_1005Metric,C11702,0402WGF1001TCE,3,
15pF,"C33,C34,C45,C46",C_0402_1005Metric,C1548,0402CG150J500NT,4,
27R,"R24,R25",R_0402_1005Metric,C138021,RC0402FR-0727RL,2,
W25Q128JVS,U8,SOIC-8_5.3x5.3mm_P1.27mm,C97521,W25Q128JVSIQ,1,
PTS810SJG250SMTRLFS,"SW1,SW2,SW3,SW4,SW5,SW6,SW7",SW_SPST_PTS810,C221895,PTS810SJG250SMTRLFS,7,
2.54-1*3P,"J2,J8",PinHeader_1x03_P2.54mm_Vertical,C49257,2.54-1*3P,2,THT
RGB,"D1,D2",LED_LiteOn_LTST-C19HE1WT,C458749,LTST-C19HE1WT,2,
330R,"R28,R41",R_0402_1005Metric,C25104,0402WGF3300TCE,2,
100R,"R29,R30,R42,R43",R_0402_1005Metric,C25076,0402WGF1000TCE,4,
PZ254V-11-04P,"J3,J7",PinHeader_1x04_P2.54mm_Vertical,C492403,PZ254V-11-04P,2,THT
4.7k,"R31,R32,R35,R36,R44,R45",R_0402_1005Metric,C25900,0402WGF4701TCE,6,
PZ254V-11-10P,"J4,J5",PinHeader_1x10_P2.54mm_Vertical,C492409,PZ254V-11-10P,2,THT
100R,"RN1,RN2",R_Array_Convex_4x0402,C48442,4D02WGJ0101TCE,2,
CH569W,U9,QFN-68-1EP_8x8mm_P0.4mm_EP5.2x5.2mm,,CH569W,1,consigned (not stocked by JLCPCB)
30MHz,Y2,Crystal_SMD_3225-4Pin_3.2x2.5mm,C70592,X322530MOB4SI,1,
CH BOOT JP,J6,PinHeader_1x02_P2.54mm_Vertical,C492401,PZ254V-11-02P,1,THT
CH EXT,J9,PinHeader_2x07_P2.54mm_Vertical,C492424,PZ254V-12-14P,1,THT
USB3 Micro-B (CH569),J10,USB3_Micro-B_Amphenol_GSB343K33HR,,GSB343K33HR,1,consigned (not stocked by JLCPCB)
microSD,J11,microSD_HC_Hirose_DM3AT-SF-PEJM5,C114218,DM3AT-SF-PEJM5,1,
